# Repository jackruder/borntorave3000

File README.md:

# borntorave3000
Gamepad keyboard with RGB backlighting and bluetooth

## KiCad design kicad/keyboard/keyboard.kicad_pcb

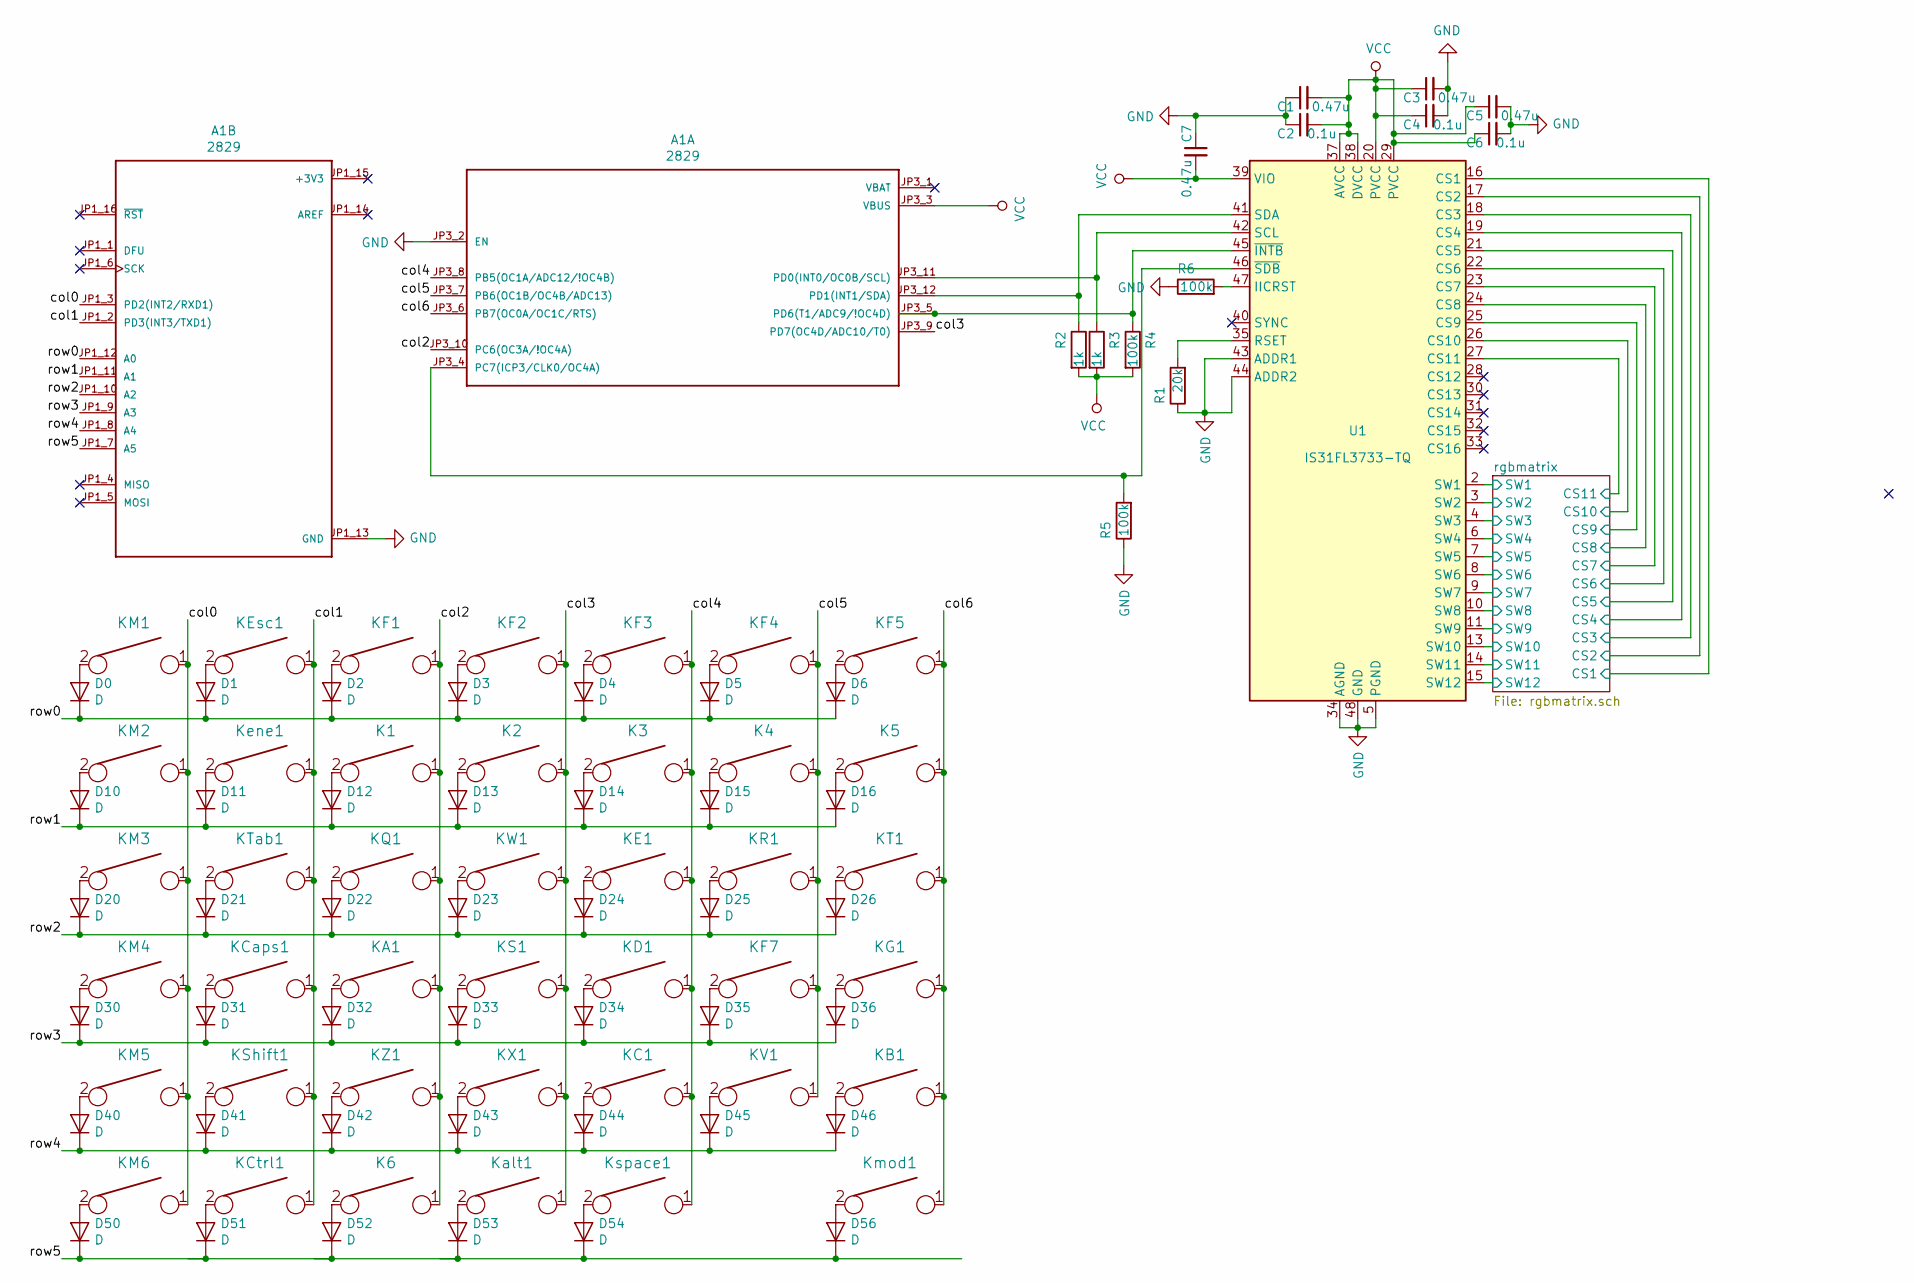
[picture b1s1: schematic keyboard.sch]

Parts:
A1: 2829; ADAFRUIT_2829
C1, C3, C5, C7: 0.47u; C_0805_2012Metric_Pad1.15x1.40mm_HandSolder
C2, C4, C6: 0.1u; C_0805_2012Metric_Pad1.15x1.40mm_HandSolder
D0, D1, D2, D3, D4, D5, D6, D10, D11, D12, D13, D14, D15, D16, D20, D21, D22, D23, D24, D25, D26, D30, D31, D32, D33, D34, D35, D36, D40, D41, D42, D43, D44, D45, D46, D50, D51, D52, D53, D54, D56: D; D_SOD123_axial
K1, K2, K3, K4, K5, K6: KEYSW; SW_Cherry_MX_1.00u_PCB
KA1: KEYSW; SW_Cherry_MX_1.00u_PCB
KB1: KEYSW; SW_Cherry_MX_1.00u_PCB
KC1: KEYSW; SW_Cherry_MX_1.00u_PCB
KCaps1: KEYSW; SW_Cherry_MX_2.00u_PCB
KCtrl1: KEYSW; SW_Cherry_MX_2.00u_PCB
KD1: KEYSW; SW_Cherry_MX_1.00u_PCB
KE1: KEYSW; SW_Cherry_MX_1.00u_PCB
KEsc1: KEYSW; SW_Cherry_MX_2.00u_PCB
KF1, KF2, KF3, KF4, KF5, KF7: KEYSW; SW_Cherry_MX_1.00u_PCB
KG1: KEYSW; SW_Cherry_MX_1.00u_PCB
KM1, KM2, KM3, KM4, KM5, KM6: KEYSW; SW_Cherry_MX_1.50u_PCB
KQ1: KEYSW; SW_Cherry_MX_1.00u_PCB
KR1: KEYSW; SW_Cherry_MX_1.00u_PCB
KS1: KEYSW; SW_Cherry_MX_1.00u_PCB
KShift1: KEYSW; SW_Cherry_MX_2.00u_PCB
KT1: KEYSW; SW_Cherry_MX_1.00u_PCB
KTab1: KEYSW; SW_Cherry_MX_2.00u_PCB
KV1: KEYSW; SW_Cherry_MX_1.00u_PCB
KW1: KEYSW; SW_Cherry_MX_1.00u_PCB
KX1: KEYSW; SW_Cherry_MX_1.00u_PCB
KZ1: KEYSW; SW_Cherry_MX_1.00u_PCB
Kalt1: KEYSW; SW_Cherry_MX_1.00u_PCB
Kene1: KEYSW; SW_Cherry_MX_2.00u_PCB
Kmod1: KEYSW; SW_Cherry_MX_1.00u_PCB
Kspace1: KEYSW; SW_Cherry_MX_2.00u_PCB
R1: 20k; R_0805_2012Metric_Pad1.15x1.40mm_HandSolder
R2, R3: 1k; R_0805_2012Metric_Pad1.15x1.40mm_HandSolder
R4, R5, R6: 100k; R_0805_2012Metric_Pad1.15x1.40mm_HandSolder
U1: IS31FL3733-TQ; TQFP-48-1EP_7x7mm_P0.5mm_EP5x5mm

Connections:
/col0: A1.JP1_3 (PD2(INT2/RXD1)), KM1.1, KM2.1, KM3.1, KM4.1, KM5.1, KM6.1
/col1: A1.JP1_2 (PD3(INT3/TXD1)), KCaps1.1, KCtrl1.1, KEsc1.1, KShift1.1, KTab1.1, Kene1.1
/col2: A1.JP3_10 (PC6(OC3A/!OC4A)), K1.1, K6.1, KA1.1, KF1.1, KQ1.1, KZ1.1
/col3: A1.JP3_9 (PD7(OC4D/ADC10/T0)), K2.1, KF2.1, KS1.1, KW1.1, KX1.1, Kalt1.1
/col4: A1.JP3_8 (PB5(OC1A/ADC12/!OC4B)), K3.1, KC1.1, KD1.1, KE1.1, KF3.1, Kspace1.1
/col5: A1.JP3_7 (PB6(OC1B/OC4B/ADC13)), K4.1, KF4.1, KF7.1, KR1.1, KV1.1
/col6: A1.JP3_6 (PB7(OC0A/OC1C/RTS)), K5.1, KB1.1, KF5.1, KG1.1, KT1.1, Kmod1.1
/rgbmatrix/CS1: U1.16 (CS1); also elsewhere on the board
/rgbmatrix/CS2: U1.17 (CS2); also elsewhere on the board
/rgbmatrix/CS3: U1.18 (CS3); also elsewhere on the board
/rgbmatrix/CS4: U1.19 (CS4); also elsewhere on the board
/rgbmatrix/CS5: U1.21 (CS5); also elsewhere on the board
/rgbmatrix/CS6: U1.22 (CS6); also elsewhere on the board
/rgbmatrix/CS7: U1.23 (CS7); also elsewhere on the board
/rgbmatrix/CS8: U1.24 (CS8); also elsewhere on the board
/rgbmatrix/CS9: U1.25 (CS9); also elsewhere on the board
/rgbmatrix/CS10: U1.26 (CS10); also elsewhere on the board
/rgbmatrix/CS11: U1.27 (CS11); also elsewhere on the board
/rgbmatrix/SW1: U1.2 (SW1); also elsewhere on the board
/rgbmatrix/SW2: U1.3 (SW2); also elsewhere on the board
/rgbmatrix/SW3: U1.4 (SW3); also elsewhere on the board
/rgbmatrix/SW4: U1.6 (SW4); also elsewhere on the board
/rgbmatrix/SW5: U1.7 (SW5); also elsewhere on the board
/rgbmatrix/SW6: U1.8 (SW6); also elsewhere on the board
/rgbmatrix/SW7: U1.9 (SW7); also elsewhere on the board
/rgbmatrix/SW8: U1.10 (SW8); also elsewhere on the board
/rgbmatrix/SW9: U1.11 (SW9); also elsewhere on the board
/rgbmatrix/SW10: U1.13 (SW10); also elsewhere on the board
/rgbmatrix/SW11: U1.14 (SW11); also elsewhere on the board
/rgbmatrix/SW12: U1.15 (SW12); also elsewhere on the board
/row0: A1.JP1_12 (A0), D0.1 (K), D1.1 (K), D2.1 (K), D3.1 (K), D4.1 (K), D5.1 (K), D6.1 (K)
/row1: A1.JP1_11 (A1), D10.1 (K), D11.1 (K), D12.1 (K), D13.1 (K), D14.1 (K), D15.1 (K), D16.1 (K)
/row2: A1.JP1_10 (A2), D20.1 (K), D21.1 (K), D22.1 (K), D23.1 (K), D24.1 (K), D25.1 (K), D26.1 (K)
/row3: A1.JP1_9 (A3), D30.1 (K), D31.1 (K), D32.1 (K), D33.1 (K), D34.1 (K), D35.1 (K), D36.1 (K)
/row4: A1.JP1_8 (A4), D40.1 (K), D41.1 (K), D42.1 (K), D43.1 (K), D44.1 (K), D45.1 (K), D46.1 (K)
/row5: A1.JP1_7 (A5), D50.1 (K), D51.1 (K), D52.1 (K), D53.1 (K), D54.1 (K), D56.1 (K)
GND: A1.JP1_13 (GND), A1.JP3_2 (EN), C1.1, C2.1, C3.2, C4.2, C5.2, C6.2, C7.1, R1.1, R5.1, R6.1, U1.5 (PGND), U1.12 (PGND), U1.34 (AGND), U1.43 (ADDR1), U1.44 (ADDR2), U1.48 (GND), U1.49 (GND)
unnamed: A1.JP3_4 (PC7(ICP3/CLK0/OC4A)), R5.2, U1.46 (~SDB)
unnamed: A1.JP3_5 (PD6(T1/ADC9/!OC4D)), R4.1, U1.45 (~INTB)
unnamed: A1.JP3_11 (PD0(INT0/OC0B/SCL)), R3.1, U1.42 (SCL)
unnamed: A1.JP3_12 (PD1(INT1/SDA)), R2.1, U1.41 (SDA)
unnamed: D0.2 (A), KM1.2
unnamed: D1.2 (A), KEsc1.2
unnamed: D2.2 (A), KF1.2
unnamed: D3.2 (A), KF2.2
unnamed: D4.2 (A), KF3.2
unnamed: D5.2 (A), KF4.2
unnamed: D6.2 (A), KF5.2
unnamed: D10.2 (A), KM2.2
unnamed: D11.2 (A), Kene1.2
unnamed: D12.2 (A), K1.2
unnamed: D13.2 (A), K2.2
unnamed: D14.2 (A), K3.2
unnamed: D15.2 (A), K4.2
unnamed: D16.2 (A), K5.2
unnamed: D20.2 (A), KM3.2
unnamed: D21.2 (A), KTab1.2
unnamed: D22.2 (A), KQ1.2
unnamed: D23.2 (A), KW1.2
unnamed: D24.2 (A), KE1.2
unnamed: D25.2 (A), KR1.2
unnamed: D26.2 (A), KT1.2
unnamed: D30.2 (A), KM4.2
unnamed: D31.2 (A), KCaps1.2
unnamed: D32.2 (A), KA1.2
unnamed: D33.2 (A), KS1.2
unnamed: D34.2 (A), KD1.2
unnamed: D35.2 (A), KF7.2
unnamed: D36.2 (A), KG1.2
unnamed: D40.2 (A), KM5.2
unnamed: D41.2 (A), KShift1.2
unnamed: D42.2 (A), KZ1.2
unnamed: D43.2 (A), KX1.2
unnamed: D44.2 (A), KC1.2
unnamed: D45.2 (A), KV1.2
unnamed: D46.2 (A), KB1.2
unnamed: D50.2 (A), KM6.2
unnamed: D51.2 (A), KCtrl1.2
unnamed: D52.2 (A), K6.2
unnamed: D53.2 (A), Kalt1.2
unnamed: D54.2 (A), Kspace1.2
unnamed: D56.2 (A), Kmod1.2
unnamed: R1.2, U1.35 (RSET)
unnamed: R6.2, U1.47 (IICRST)
VCC: A1.JP3_3 (VBUS), C1.2, C2.2, C3.1, C4.1, C5.1, C6.1, C7.2, R2.2, R3.2, R4.2, U1.20 (PVCC), U1.29 (PVCC), U1.37 (AVCC), U1.38 (DVCC), U1.39 (VIO)

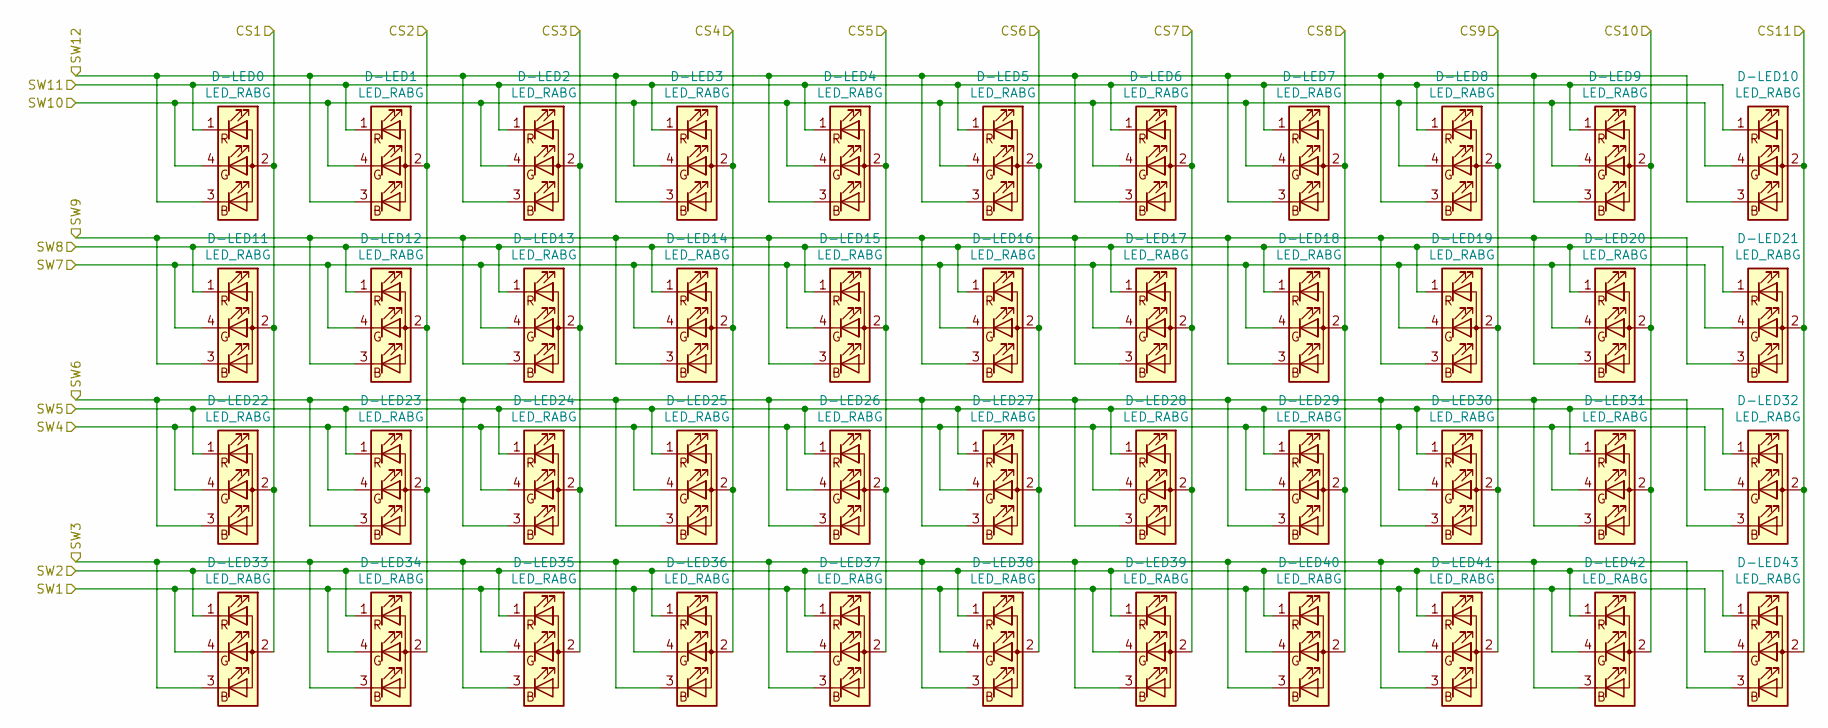
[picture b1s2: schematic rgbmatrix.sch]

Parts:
D-LED0, D-LED1, D-LED2, D-LED3, D-LED4, D-LED5, D-LED6, D-LED7, D-LED8, D-LED9, D-LED10, D-LED11, D-LED12, D-LED13, D-LED14, D-LED15, D-LED16, D-LED17, D-LED18, D-LED19, D-LED20, D-LED21, D-LED22, D-LED23, D-LED24, D-LED25, D-LED26, D-LED27, D-LED28, D-LED29, D-LED30, D-LED31, D-LED32, D-LED33, D-LED34, D-LED35, D-LED36, D-LED37, D-LED38, D-LED39, D-LED40, D-LED41, D-LED42, D-LED43: LED_RABG; rev_mountLED_SMD_RGB

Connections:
/rgbmatrix/CS1: D-LED0.2 (A), D-LED11.2 (A), D-LED22.2 (A), D-LED33.2 (A); also elsewhere on the board
/rgbmatrix/CS2: D-LED1.2 (A), D-LED12.2 (A), D-LED23.2 (A), D-LED34.2 (A); also elsewhere on the board
/rgbmatrix/CS3: D-LED2.2 (A), D-LED13.2 (A), D-LED24.2 (A), D-LED35.2 (A); also elsewhere on the board
/rgbmatrix/CS4: D-LED3.2 (A), D-LED14.2 (A), D-LED25.2 (A), D-LED36.2 (A); also elsewhere on the board
/rgbmatrix/CS5: D-LED4.2 (A), D-LED15.2 (A), D-LED26.2 (A), D-LED37.2 (A); also elsewhere on the board
/rgbmatrix/CS6: D-LED5.2 (A), D-LED16.2 (A), D-LED27.2 (A), D-LED38.2 (A); also elsewhere on the board
/rgbmatrix/CS7: D-LED6.2 (A), D-LED17.2 (A), D-LED28.2 (A), D-LED39.2 (A); also elsewhere on the board
/rgbmatrix/CS8: D-LED7.2 (A), D-LED18.2 (A), D-LED29.2 (A), D-LED40.2 (A); also elsewhere on the board
/rgbmatrix/CS9: D-LED8.2 (A), D-LED19.2 (A), D-LED30.2 (A), D-LED41.2 (A); also elsewhere on the board
/rgbmatrix/CS10: D-LED9.2 (A), D-LED20.2 (A), D-LED31.2 (A), D-LED42.2 (A); also elsewhere on the board
/rgbmatrix/CS11: D-LED10.2 (A), D-LED21.2 (A), D-LED32.2 (A), D-LED43.2 (A); also elsewhere on the board
/rgbmatrix/SW1: D-LED33.4 (GK), D-LED34.4 (GK), D-LED35.4 (GK), D-LED36.4 (GK), D-LED37.4 (GK), D-LED38.4 (GK), D-LED39.4 (GK), D-LED40.4 (GK), D-LED41.4 (GK), D-LED42.4 (GK), D-LED43.4 (GK); also elsewhere on the board
/rgbmatrix/SW2: D-LED33.1 (RK), D-LED34.1 (RK), D-LED35.1 (RK), D-LED36.1 (RK), D-LED37.1 (RK), D-LED38.1 (RK), D-LED39.1 (RK), D-LED40.1 (RK), D-LED41.1 (RK), D-LED42.1 (RK), D-LED43.1 (RK); also elsewhere on the board
/rgbmatrix/SW3: D-LED33.3 (BK), D-LED34.3 (BK), D-LED35.3 (BK), D-LED36.3 (BK), D-LED37.3 (BK), D-LED38.3 (BK), D-LED39.3 (BK), D-LED40.3 (BK), D-LED41.3 (BK), D-LED42.3 (BK), D-LED43.3 (BK); also elsewhere on the board
/rgbmatrix/SW4: D-LED22.4 (GK), D-LED23.4 (GK), D-LED24.4 (GK), D-LED25.4 (GK), D-LED26.4 (GK), D-LED27.4 (GK), D-LED28.4 (GK), D-LED29.4 (GK), D-LED30.4 (GK), D-LED31.4 (GK), D-LED32.4 (GK); also elsewhere on the board
/rgbmatrix/SW5: D-LED22.1 (RK), D-LED23.1 (RK), D-LED24.1 (RK), D-LED25.1 (RK), D-LED26.1 (RK), D-LED27.1 (RK), D-LED28.1 (RK), D-LED29.1 (RK), D-LED30.1 (RK), D-LED31.1 (RK), D-LED32.1 (RK); also elsewhere on the board
/rgbmatrix/SW6: D-LED22.3 (BK), D-LED23.3 (BK), D-LED24.3 (BK), D-LED25.3 (BK), D-LED26.3 (BK), D-LED27.3 (BK), D-LED28.3 (BK), D-LED29.3 (BK), D-LED30.3 (BK), D-LED31.3 (BK), D-LED32.3 (BK); also elsewhere on the board
/rgbmatrix/SW7: D-LED11.4 (GK), D-LED12.4 (GK), D-LED13.4 (GK), D-LED14.4 (GK), D-LED15.4 (GK), D-LED16.4 (GK), D-LED17.4 (GK), D-LED18.4 (GK), D-LED19.4 (GK), D-LED20.4 (GK), D-LED21.4 (GK); also elsewhere on the board
/rgbmatrix/SW8: D-LED11.1 (RK), D-LED12.1 (RK), D-LED13.1 (RK), D-LED14.1 (RK), D-LED15.1 (RK), D-LED16.1 (RK), D-LED17.1 (RK), D-LED18.1 (RK), D-LED19.1 (RK), D-LED20.1 (RK), D-LED21.1 (RK); also elsewhere on the board
/rgbmatrix/SW9: D-LED11.3 (BK), D-LED12.3 (BK), D-LED13.3 (BK), D-LED14.3 (BK), D-LED15.3 (BK), D-LED16.3 (BK), D-LED17.3 (BK), D-LED18.3 (BK), D-LED19.3 (BK), D-LED20.3 (BK), D-LED21.3 (BK); also elsewhere on the board
/rgbmatrix/SW10: D-LED0.4 (GK), D-LED1.4 (GK), D-LED2.4 (GK), D-LED3.4 (GK), D-LED4.4 (GK), D-LED5.4 (GK), D-LED6.4 (GK), D-LED7.4 (GK), D-LED8.4 (GK), D-LED9.4 (GK), D-LED10.4 (GK); also elsewhere on the board
/rgbmatrix/SW11: D-LED0.1 (RK), D-LED1.1 (RK), D-LED2.1 (RK), D-LED3.1 (RK), D-LED4.1 (RK), D-LED5.1 (RK), D-LED6.1 (RK), D-LED7.1 (RK), D-LED8.1 (RK), D-LED9.1 (RK), D-LED10.1 (RK); also elsewhere on the board
/rgbmatrix/SW12: D-LED0.3 (BK), D-LED1.3 (BK), D-LED2.3 (BK), D-LED3.3 (BK), D-LED4.3 (BK), D-LED5.3 (BK), D-LED6.3 (BK), D-LED7.3 (BK), D-LED8.3 (BK), D-LED9.3 (BK), D-LED10.3 (BK); also elsewhere on the board

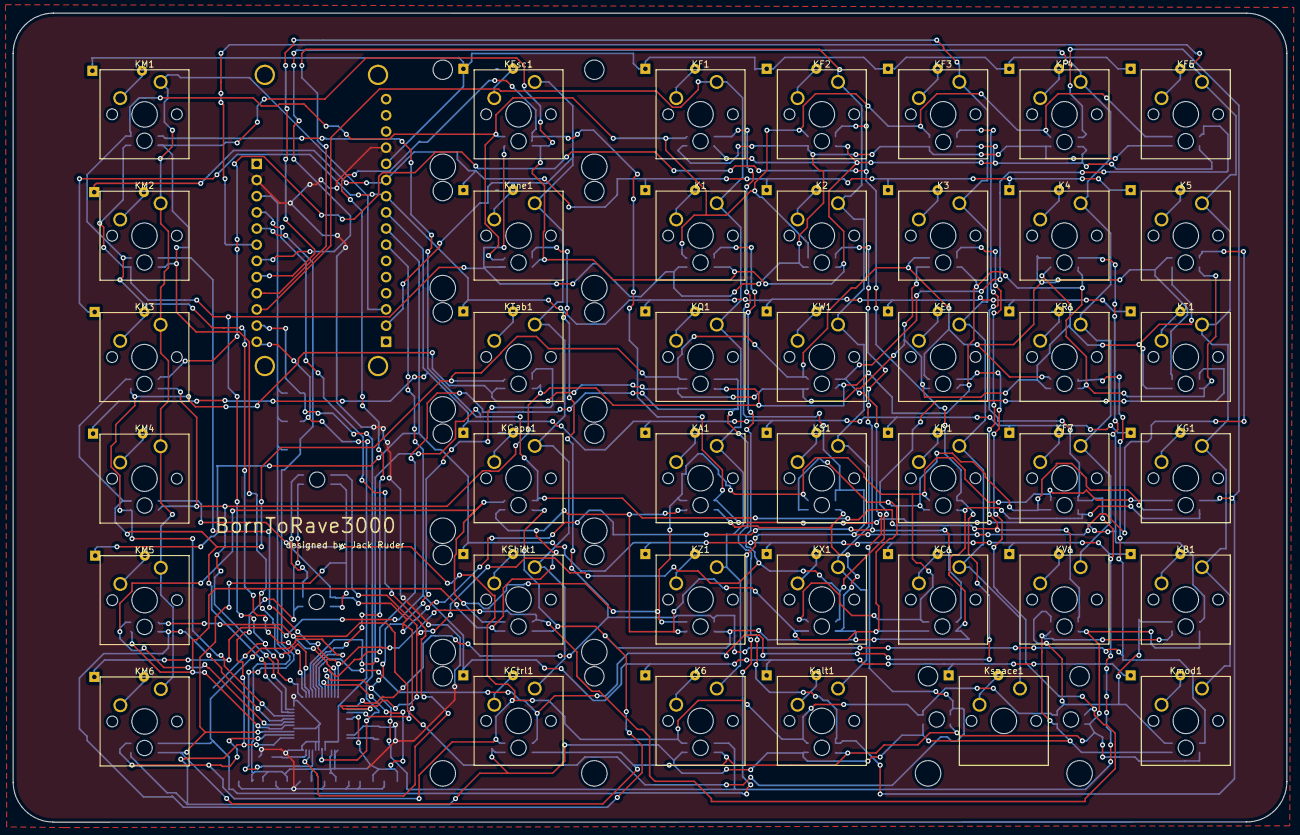
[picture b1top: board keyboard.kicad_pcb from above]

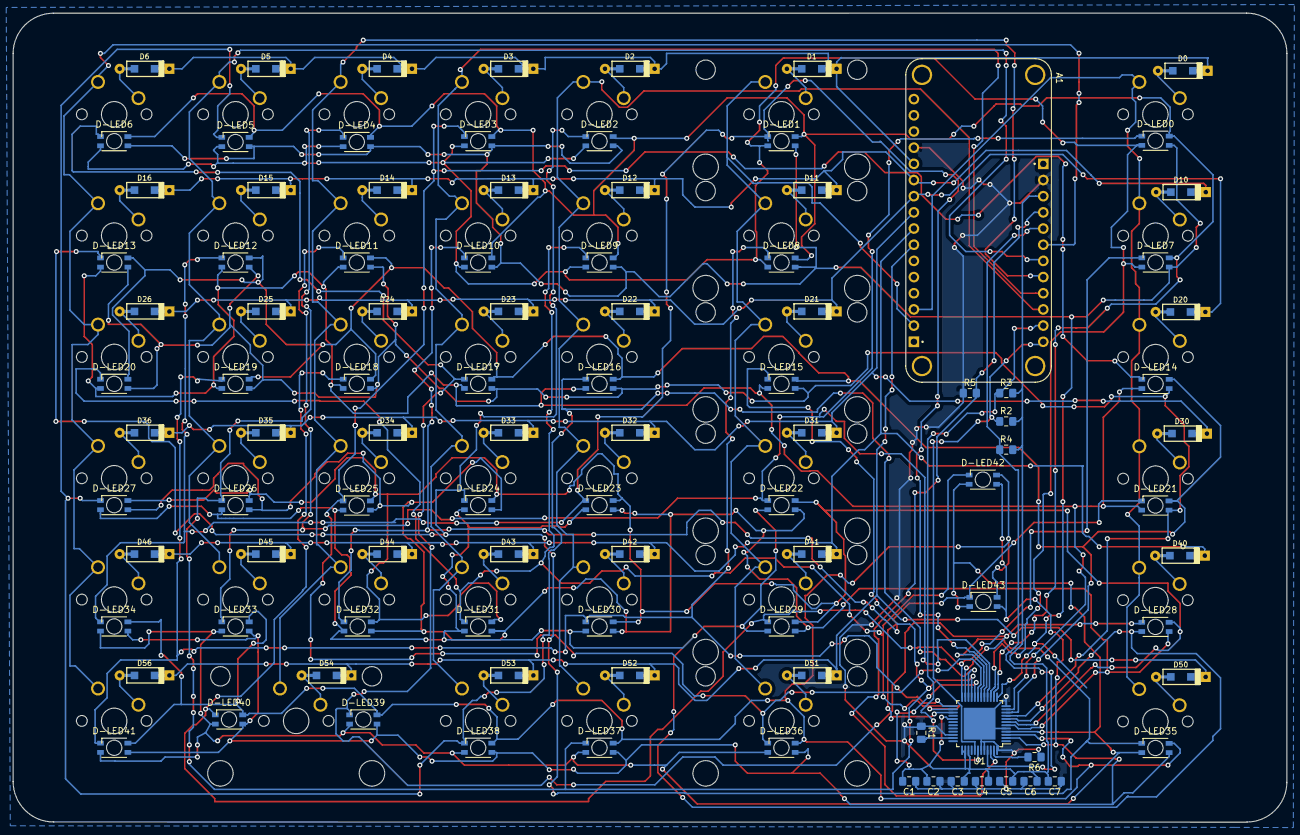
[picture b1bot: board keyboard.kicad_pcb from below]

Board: 2 copper layers, 200.0 x 127.0 mm, 141 parts (100 on the bottom side), 85 nets.

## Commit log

2020-04-06 Added files, first commit
2020-04-07 fixed borders, added text to pcb
